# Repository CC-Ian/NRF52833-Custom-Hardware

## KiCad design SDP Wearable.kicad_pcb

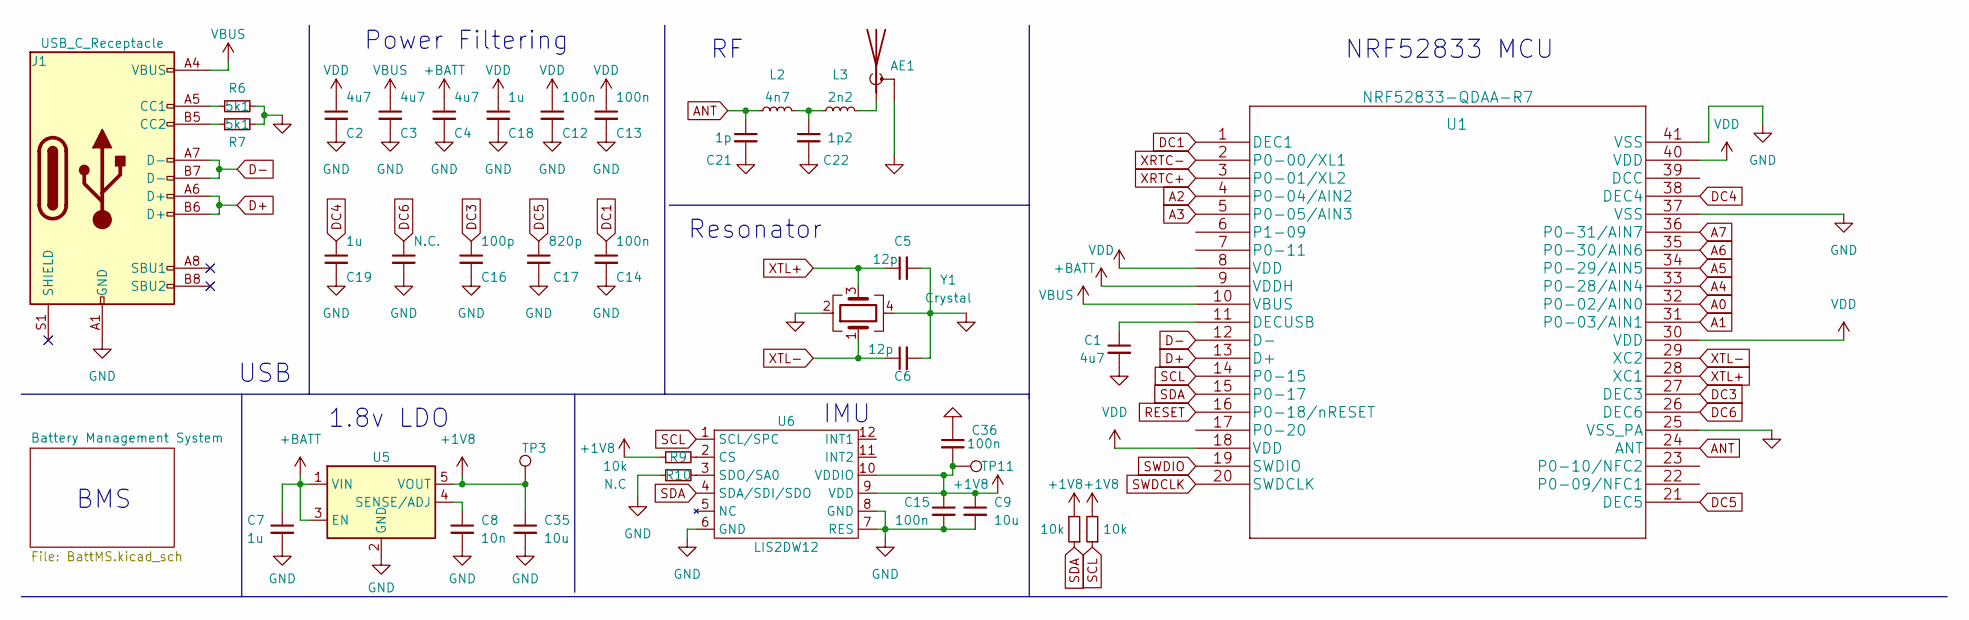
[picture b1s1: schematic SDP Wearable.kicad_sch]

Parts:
AE1: Antenna_Shield; Texas_SWRA117D_2.4GHz_Left
C1, C2, C3, C4: 4u7; C_0402_1005Metric
C5, C6: 12p; C_0402_1005Metric
C7, C18, C19: 1u; C_0402_1005Metric
C8: 10n; C_0402_1005Metric
C9: 10u; C_0603_1608Metric
C12, C13, C14, C15, C36: 100n; C_0402_1005Metric
C16: 100p; C_0402_1005Metric
C17: 820p; C_0402_1005Metric
C21: 1p; C_0402_1005Metric
C22: 1p2; C_0402_1005Metric
C32: N.C.; C_0402_1005Metric
C35: 10u; C_0402_1005Metric
J1: USB_C_Receptacle; USB_C_Receptacle_HRO_TYPE-C-31-M-12
L2: 4n7; L_0402_1005Metric
L3: 2n2; L_0402_1005Metric
R6, R7: 5k1; R_0402_1005Metric
R8, R9, R11: 10k; R_0402_1005Metric
R10: N.C; R_0402_1005Metric
TP3, TP11: TestPoint; TestPoint_Pad_D1.0mm
U1: NRF52833-QDAA-R7; QFN-40-1EP_5x5mm_P0.4mm_EP3.6x3.6mm_ThermalVias
U5: BCT2019EXKV18-TR; TSOT-23-5
U6: LIS2DW12; LGA-12_2x2mm_P0.5mm
Y1: Crystal; Crystal_SMD_2016-4Pin_2.0x1.6mm

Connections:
+1V8: C9.1, C15.1, C35.1, C36.2, R8.2, R9.1, R11.2, TP3.1, TP11.1, U5.5 (VOUT), U6.9 (VDD), U6.10 (VDDIO)
+BATT: C4.1, C7.1, U1.9 (VDDH), U5.1 (VIN), U5.3 (EN); also elsewhere on the board
A0: U1.32 (P0-02/AIN0)
A1: U1.31 (P0-03/AIN1)
A2: U1.4 (P0-04/AIN2)
A3: U1.5 (P0-05/AIN3)
A4: U1.33 (P0-28/AIN4)
A5: U1.34 (P0-29/AIN5)
A6: U1.35 (P0-30/AIN6)
A7: U1.36 (P0-31/AIN7)
ANT: C21.1, L2.1, U1.24 (ANT)
D+: J1.A6 (D+), J1.B6 (D+), U1.13 (D+)
D-: J1.A7 (D-), J1.B7 (D-), U1.12 (D-)
DC1: C14.1, U1.1 (DEC1)
DC3: C16.1, U1.27 (DEC3)
DC4: C19.1, U1.38 (DEC4)
DC5: C17.1, U1.21 (DEC5)
DC6: C32.1, U1.26 (DEC6)
GND: AE1.2 (Shield), C1.2, C2.2, C3.2, C4.2, C5.2, C6.2, C7.2, C8.2, C9.2, C12.2, C13.2, C14.2, C15.2, C16.2, C17.2, C18.2, C19.2, C21.2, C22.2, C32.2, C35.2, C36.1, J1.A1 (GND), J1.A12 (GND), J1.B1 (GND), J1.B12 (GND), R6.2, R7.2, R10.1, U1.25 (VSS_PA), U1.37 (VSS), U1.41 (VSS), U5.2 (GND), U6.6 (GND), U6.7 (RES), U6.8 (GND), Y1.2, Y1.4; also elsewhere on the board
unnamed: AE1.1 (A), L3.2
unnamed: C1.1, U1.11 (DECUSB)
unnamed: C8.1, U5.4 (SENSE/ADJ)
unnamed: C22.1, L2.2, L3.1
unnamed: J1.A5 (CC1), R6.1
unnamed: J1.B5 (CC2), R7.1
unnamed: R9.2, U6.2 (CS)
unnamed: R10.2, U6.3 (SDO/SA0)
RESET: U1.16 (P0-18/nRESET)
SCL: R11.1, U1.14 (P0-15), U6.1 (SCL/SPC)
SDA: R8.1, U1.15 (P0-17), U6.4 (SDA/SDI/SDO)
SWDCLK: U1.20 (SWDCLK)
SWDIO: U1.19 (SWDIO)
VBUS: C3.1, J1.A4 (VBUS), J1.A9 (VBUS), J1.B4 (VBUS), J1.B9 (VBUS), U1.10 (VBUS); also elsewhere on the board
VDD: C2.1, C12.1, C13.1, C18.1, U1.8 (VDD), U1.18 (VDD), U1.30 (VDD), U1.40 (VDD)
XRTC+: U1.3 (P0-01/XL2)
XRTC-: U1.2 (P0-00/XL1)
XTL+: C5.1, U1.28 (XC1), Y1.3
XTL-: C6.1, U1.29 (XC2), Y1.1

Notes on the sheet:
Power Filtering
NRF52833 MCU
Resonator
1.8v LDO
USB
BMS
IMU

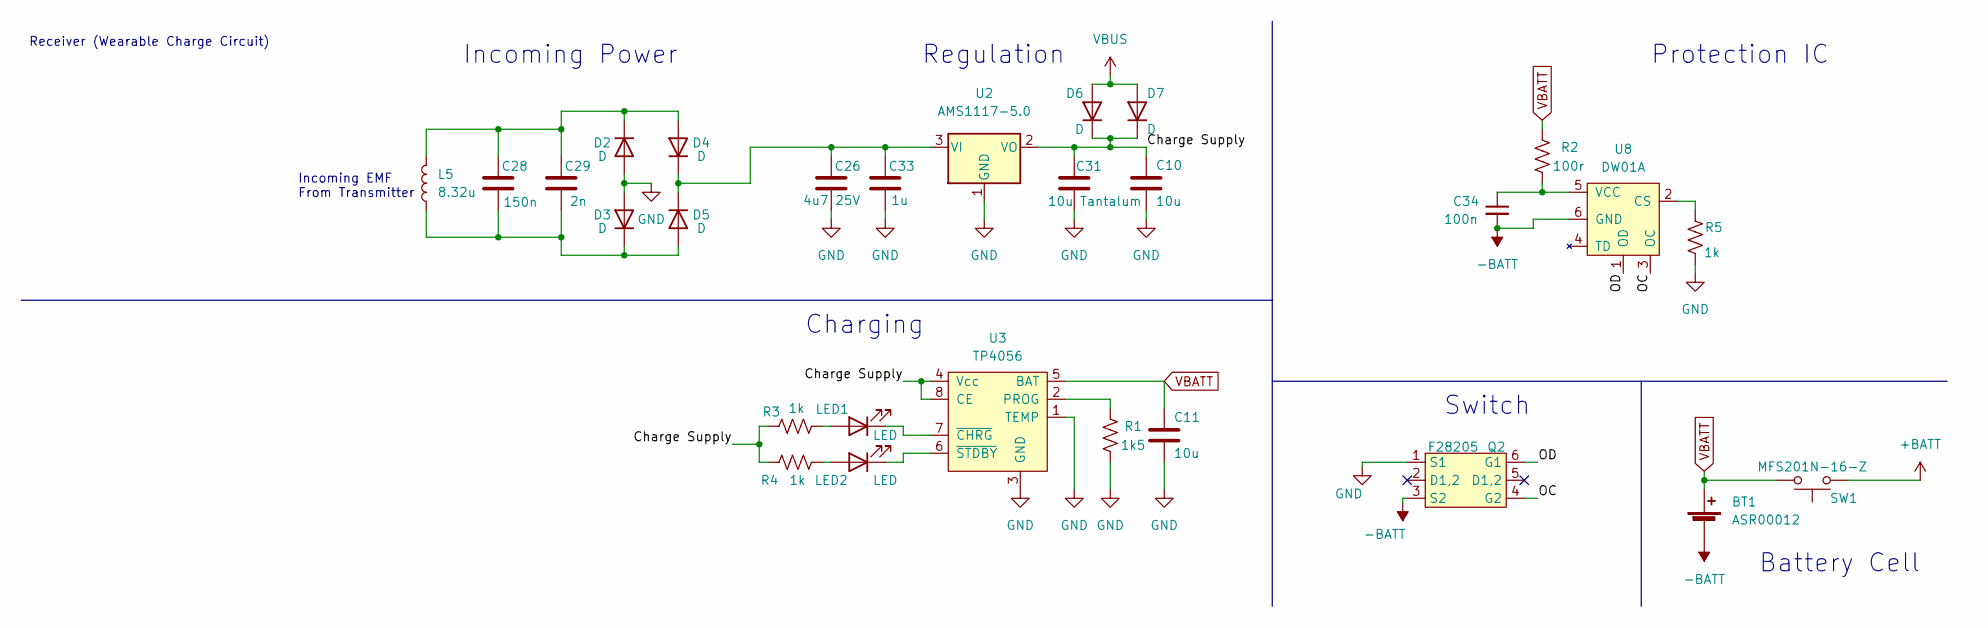
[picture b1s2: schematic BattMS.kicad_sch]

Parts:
BT1: ASR00012; PinHeader_1x02_P2.54mm_Vertical
C10, C11: 10u; C_0603_1608Metric
C26: 4u7 25V; C_0603_1608Metric
C28: 150n; C_1206_3216Metric
C29: 2n; C_0603_1608Metric
C31: 10u Tantalum; C_0805_2012Metric
C33: 1u; C_0402_1005Metric
C34: 100n; C_0402_1005Metric
D2, D3, D4, D5, D6, D7: D; DIN1006-2
L5: 8.32u; PinHeader_1x02_P2.54mm_Vertical
LED1, LED2: LED; LED_0402_1005Metric
Q2: F28205; SOT-23-6
R1: 1k5; R_0402_1005Metric
R2: 100r; R_0402_1005Metric
R3, R4, R5: 1k; R_0402_1005Metric
SW1: MFS201N-16-Z; SW_SPDT_PCM12
U2: AMS1117-5.0; SOT-223-3_TabPin2
U3: TP4056; SOP-8_3.9x4.9mm_P1.27mm
U8: DW01A; SOT-23-6

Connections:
+BATT: SW1.1 (A), SW1.2 (A); also elsewhere on the board
-BATT: BT1.1 (-), C34.2, Q2.3 (S2), U8.6 (GND)
/Battery Management System/Charge Supply: C10.1, C31.1, D6.1 (K), D7.1 (K), R3.1, R4.1, U2.2 (VO), U3.4 (Vcc), U3.8 (CE)
/Battery Management System/OC: Q2.4 (G2), U8.3 (OC)
/Battery Management System/OD: Q2.6 (G1), U8.1 (OD)
GND: C10.2, C11.2, C26.2, C31.2, C33.2, D2.2 (A), D3.2 (A), Q2.1 (S1), R1.2, R5.2, U2.1 (GND), U3.1 (TEMP), U3.3 (GND); also elsewhere on the board
unnamed: C26.1, C33.1, D4.1 (K), D5.1 (K), U2.3 (VI)
unnamed: C28.1, C29.1, D2.1 (K), D4.2 (A), L5.2
unnamed: C28.2, C29.2, D3.1 (K), D5.2 (A), L5.1
unnamed: C34.1, R2.2, U8.5 (VCC)
unnamed: LED1.1 (K), U3.7 (~CHRG)
unnamed: LED1.2 (A), R3.2
unnamed: LED2.1 (K), U3.6 (~STDBY)
unnamed: LED2.2 (A), R4.2
unnamed: R1.1, U3.2 (PROG)
unnamed: R5.1, U8.2 (CS)
VBATT: BT1.2 (+), C11.1, R2.1, SW1.3 (B), SW1.4 (B), U3.5 (BAT)
VBUS: D6.2 (A), D7.2 (A); also elsewhere on the board

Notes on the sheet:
Receiver (Wearable Charge Circuit)
Charging
Switch
Incoming EMF From Transmitter
Protection IC
Incoming Power
Regulation
Battery Cell

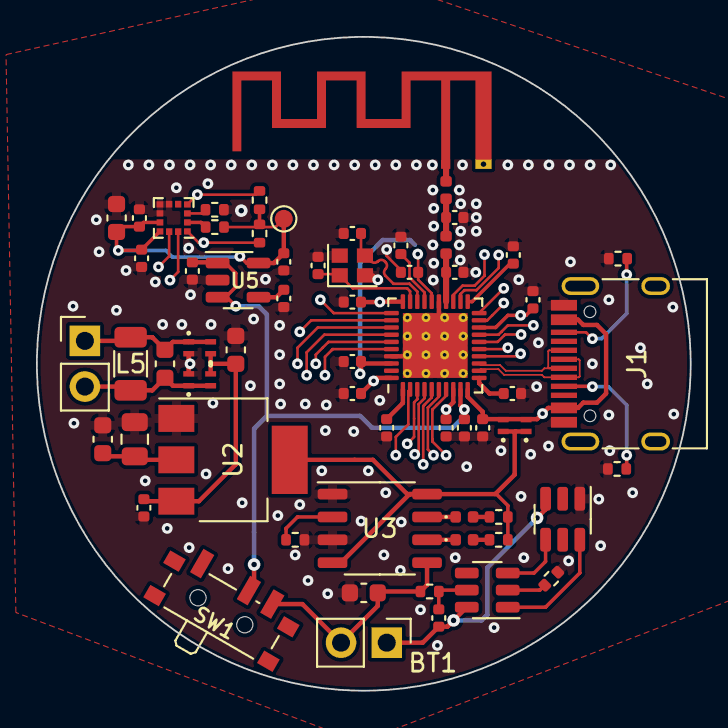
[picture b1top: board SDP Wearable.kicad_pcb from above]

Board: 4 copper layers, 36.3 x 36.3 mm, 65 parts (0 on the bottom side), 40 nets.

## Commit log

2023-02-16 Added PCB Design Files
2023-02-16 Added F_CU Picture
